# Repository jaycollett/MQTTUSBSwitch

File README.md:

# MQTTUSBSwitch

MQTT Enabled USB Switch to remotely connect/disconnect USB devices. This firmware and hardware attempts to mimic the actual pin connect/disconnect sequence that occurs when physically inserting or removing a USB plug. The board uses USB 3.0 connectors but only supports USB 2.0. Future versions will correctly switch the extra SS data pins so it will support USB 3.0. 

# Schematic 

# Board

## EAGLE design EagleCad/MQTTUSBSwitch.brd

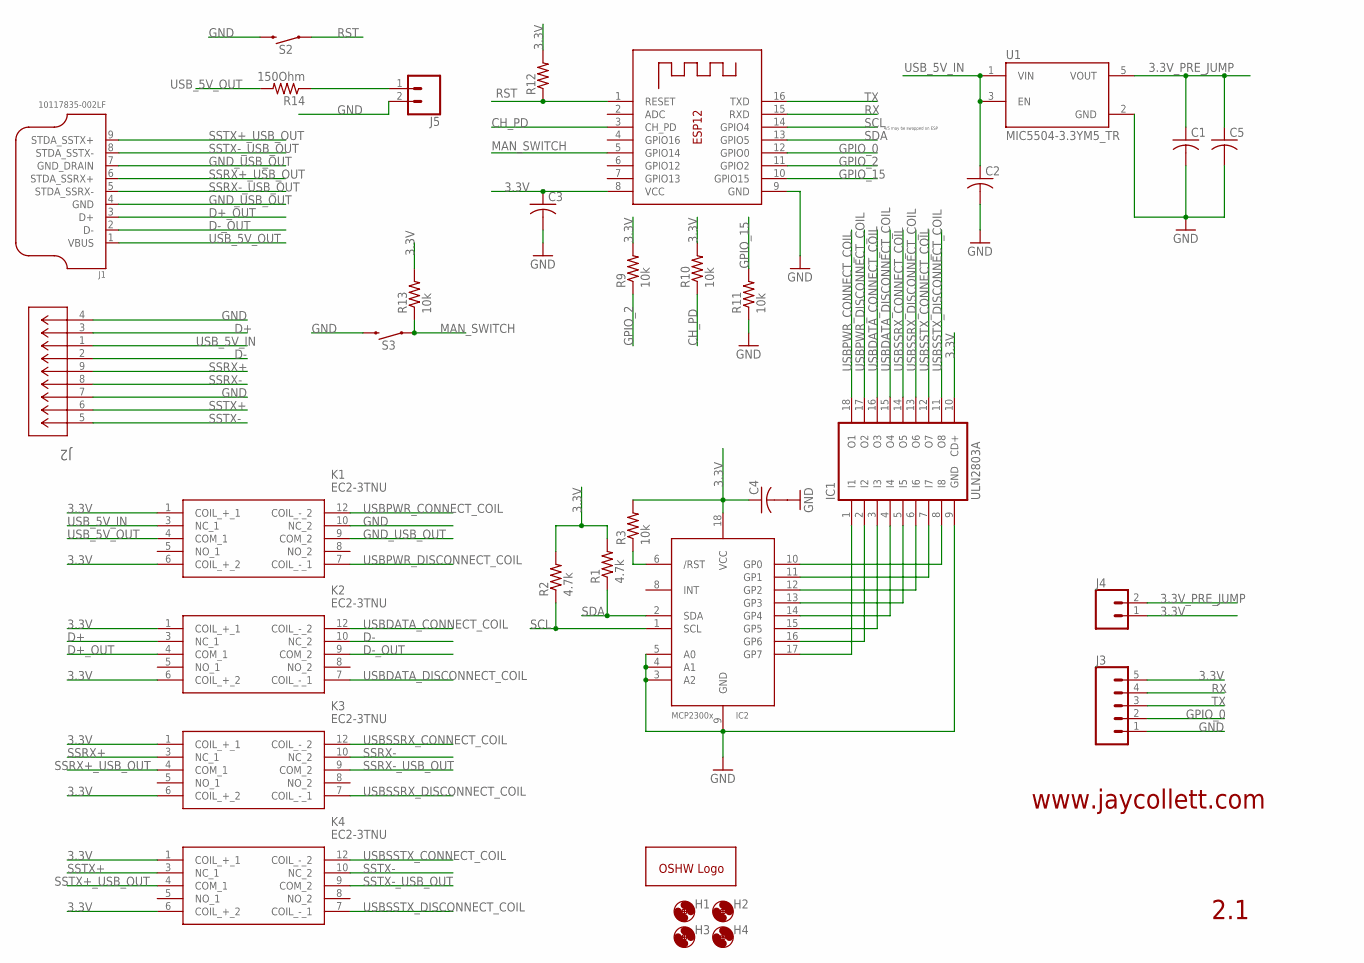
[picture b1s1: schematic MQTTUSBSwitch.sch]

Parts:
C1, C2, C3, C4, C5: C-USC0805; C0805
GOLD_ORB_SM1: OSHWLOGOLOGO5MM; OSHW_5MM
H1, H2, H3, H4: MOUNT-HOLE3.0; 3,0
IC1: ULN2803A; DIL18
IC2: MCP23008/P; DIL18
J1: 10117835-002LF; FCI_10117835-002LF
J2: GSB4211311WEU; CONN9_1311WEU_AMP
J3: CONN_05; 1X05
J4, J5: CONN_02; 1X02
K1, K2, K3, K4: EC2-3TNU; EC23TNU
R1, R2: 4.7k; R0805
R3, R9, R10, R11, R13: 10k; R0805
R12: R-US_R0805; R0805
R14: 150Ohm; R0805
S2, S3: MOMENTARY-SWITCH-SPST-PTH-6.0MM-KIT; TACTILE_SWITCH_PTH_6.0MM_KIT
U1: MIC5504-3.3YM5_TR; SOT95P280X145-5N
X1: ESP-12

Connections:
3.3V: C3.1, C4.1, IC1.10 (CD+), IC2.18 (VCC), J3.5, J4.1, K1.1 (COIL_+_1), K1.6 (COIL_+_2), K2.1 (COIL_+_1), K2.6 (COIL_+_2), K3.1 (COIL_+_1), K3.6 (COIL_+_2), K4.1 (COIL_+_1), K4.6 (COIL_+_2), R1.2, R2.2, R3.2, R9.2, R10.2, R12.2, R13.2, X1.8 (VCC)
3.3V_PRE_JUMP: C1.1, C5.1, J4.2, U1.5 (VOUT)
CH_PD: R10.1, X1.3 (CH_PD)
D+: J2.3, K2.3 (NC_1)
D+_OUT: J1.3 (D+), K2.4 (COM_1)
D-: J2.2, K2.10 (NC_2)
D-_OUT: J1.2 (D-), K2.9 (COM_2)
GND: C1.2, C2.2, C3.2, C4.2, C5.2, IC1.9 (GND), IC2.3 (A2), IC2.4 (A1), IC2.5 (A0), IC2.9 (GND), J2.4, J2.7, J3.1, J5.2, K1.10 (NC_2), R11.1, S2.3 (2), S3.3 (2), U1.2 (GND), X1.9 (GND)
GND_USB_OUT: J1.4 (GND), J1.7 (GND_DRAIN), K1.9 (COM_2)
GPIO_0: J3.2, X1.12 (GPIO0)
GPIO_2: R9.1, X1.11 (GPIO2)
GPIO_15: R11.2, X1.10 (GPIO15)
MAN_SWITCH: R13.1, S3.1, X1.5 (GPIO14)
unnamed: J5.1, R14.1
unnamed: IC1.8 (I8), IC2.10 (GP0)
unnamed: IC1.7 (I7), IC2.11 (GP1)
unnamed: IC1.6 (I6), IC2.12 (GP2)
unnamed: IC1.5 (I5), IC2.13 (GP3)
unnamed: IC1.4 (I4), IC2.14 (GP4)
unnamed: IC1.3 (I3), IC2.15 (GP5)
unnamed: IC1.2 (I2), IC2.16 (GP6)
unnamed: IC1.1 (I1), IC2.17 (GP7)
unnamed: IC2.6 (/RST), R3.1
RST: R12.1, S2.1, X1.1 (RESET)
RX: J3.4, X1.15 (RXD)
SCL: IC2.1 (SCL), R2.1, X1.14 (GPIO4)
SDA: IC2.2 (SDA), R1.1, X1.13 (GPIO5)
SSRX+: J2.9, K3.3 (NC_1)
SSRX+_USB_OUT: J1.6 (STDA_SSRX+), K3.4 (COM_1)
SSRX-: J2.8, K3.10 (NC_2)
SSRX-_USB_OUT: J1.5 (STDA_SSRX-), K3.9 (COM_2)
SSTX+: J2.6, K4.3 (NC_1)
SSTX+_USB_OUT: J1.9 (STDA_SSTX+), K4.4 (COM_1)
SSTX-: J2.5, K4.10 (NC_2)
SSTX-_USB_OUT: J1.8 (STDA_SSTX-), K4.9 (COM_2)
TX: J3.3, X1.16 (TXD)
USBDATA_CONNECT_COIL: IC1.16 (O3), K2.12 (COIL_-_2)
USBDATA_DISCONNECT_COIL: IC1.15 (O4), K2.7 (COIL_-_1)
USBPWR_CONNECT_COIL: IC1.18 (O1), K1.12 (COIL_-_2)
USBPWR_DISCONNECT_COIL: IC1.17 (O2), K1.7 (COIL_-_1)
USBSSRX_CONNECT_COIL: IC1.14 (O5), K3.12 (COIL_-_2)
USBSSRX_DISCONNECT_COIL: IC1.13 (O6), K3.7 (COIL_-_1)
USBSSTX_CONNECT_COIL: IC1.12 (O7), K4.12 (COIL_-_2)
USBSSTX_DISCONNECT_COIL: IC1.11 (O8), K4.7 (COIL_-_1)
USB_5V_IN: C2.1, J2.1, K1.3 (NC_1), U1.1 (VIN), U1.3 (EN)
USB_5V_OUT: J1.1 (VBUS), K1.4 (COM_1), R14.2

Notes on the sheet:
2.1
www.jaycollett.com
4/5 may be swapped on ESP

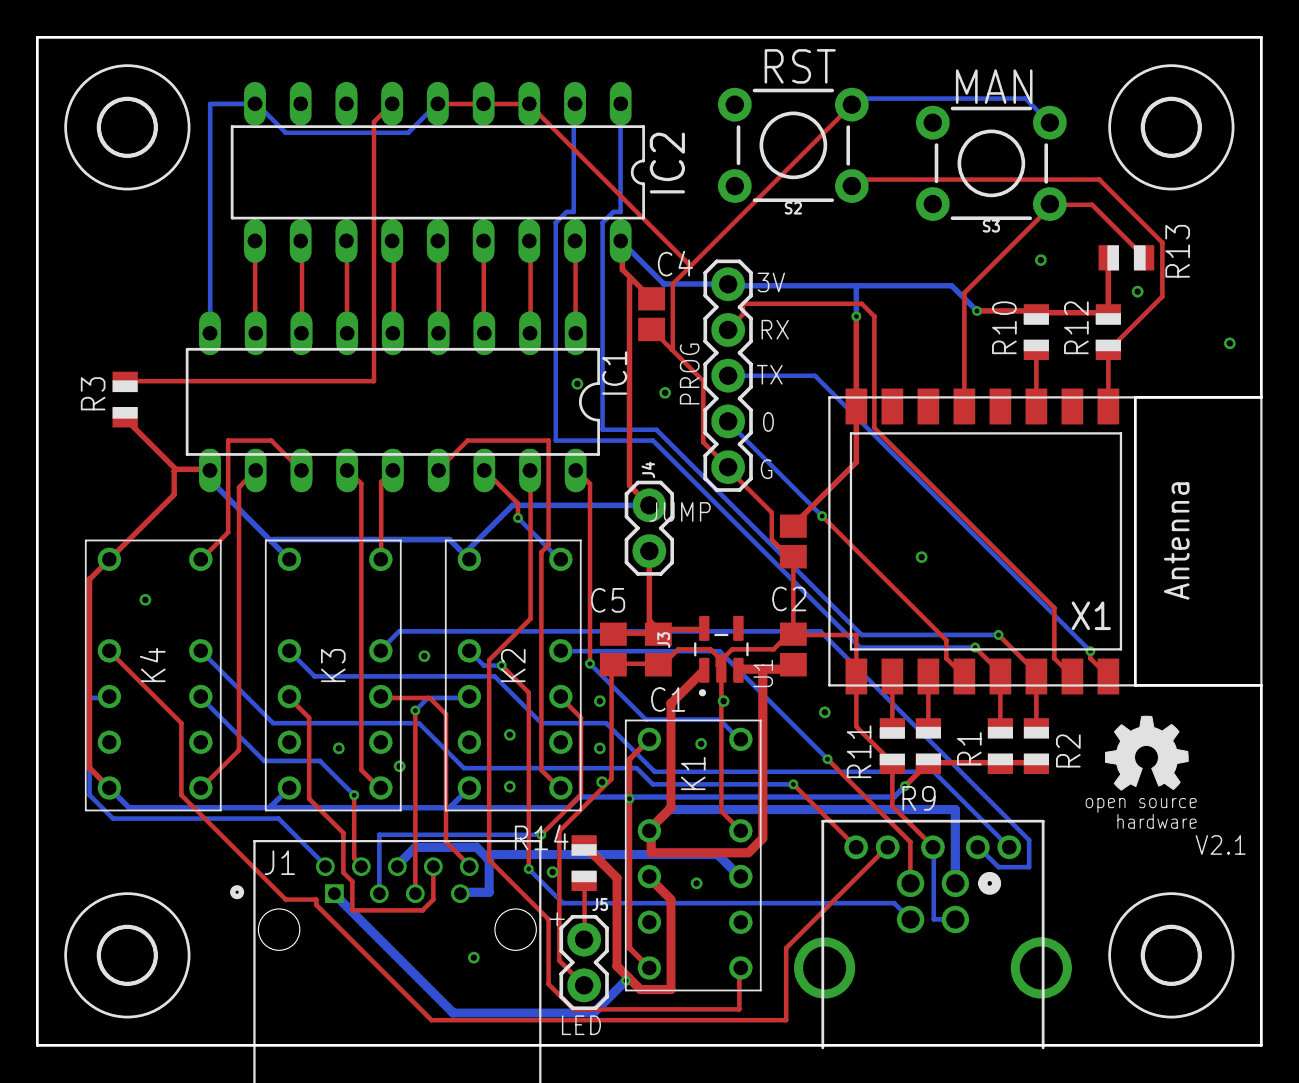
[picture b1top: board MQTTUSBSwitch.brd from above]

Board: 2 copper layers, 68.0 x 56.0 mm, 34 parts (0 on the bottom side), 46 nets.

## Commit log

2021-01-03 initial project commit
2021-01-03 Update case enclosure to have two screws per side
2021-01-03 Minor tweaks to wifimanager timeout
2021-01-08 fix board issue with ground airwires and soldermask exposing ground plane
2021-01-08 Fix issue with firmware and disconnect method
2021-01-09 Fix the swapped pins for connect/disconnect of data and power
2021-01-09 add mqtt message and topic for why we switched (mqtt, manual switch, or device reset)
2021-01-09 rename arduino folder to remove space
2021-01-10 first pass at v2.1 which simplifies relay driving with a unla2803 and a port expander to only use 2 GPIO pins on ESP8266
2021-01-11 add json code for publishing mqtt attributes
2021-01-11 New layout and routing for v2.1

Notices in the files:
parts and their libraries:
SparkFun-Connectors: Licensing: Creative Commons ShareAlike 4.0 International - https://creativecommons.org/licenses/by-sa/4.0
COPYRIGHT: Copyright (C) 2018 Accelerated Designs. All rights reserved
